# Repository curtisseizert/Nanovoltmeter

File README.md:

# Nanovoltmeter
A low noise nanovoltmeter design files and code

The design includes five boards:
1. The nanovoltmeter main board
2. A SMPS daughter board to downconvert the battery voltage to the various power rails used in the design
3. A battery board with BMS for 4S 21700 cells
4. A rear panel board with battery charger
5. A front panel

This repository will also include the source code for the STM32U575 microcontroller that interfaces with the various peripherals.

Note: The current revision of the board does not work without modifications, but the schematic has been annotated to include these. This project should still be considered in a development state, but the entirety of the design is provided here for anyone seeking to draw upon this work in low-noise, high-resolution voltage sensing projects.

Curent Status
-------------
A revision C to the board is in a stage of occasional development as I finish another project. The new revision will seek to improve the robustness of the design, addressing issues such as the apparent sensitivity to common-mode noise, inadequate power protection leading to cascade failures with certain faults, and minor drift related to battery discharge. I am looking into an improved method of retrieving SPI data from ADC conversions that should allow operation at the maximum sample rate of the AD4030-24 (2 MSPS), to reduce noise and reduce the possibility of aliasing. The revision also includes a minor redesign of the key frontend amplifier to improve gain and stability. The ADR1399 reference option will be removed from this revision.

Version 2.0 of the FW improves handling of results and user inputs, as well as reduces the load on the CPU by making better use of DMA. Unit testing is ongoing and some features are not yet implemented, but they will be coming soon. The command structure uses a SCPI-like syntax but is not fully SCPI-compliant. The improved FW should facilitate more performance testing.

I have built two of these boards, one with an LTC6655 reference, the other with an ADR1399. I have tested the noise and offset performance of the latter both with internal shorts and an external 1 mV reference. Getting both boards to work has required some changes, and I have made the appropriate edits to a revision C schematic though I have not laid this out. The noise and temperature sensitivity of the LTC6655 board is superior for internal shorts. 

Design Background
-----------------

A proof of concept model of the input stage was previously prepared, which showed a flat NSD of approximately 1.2 nV/sqrt(Hz). At 1 sample per second, the peak to peak noise was about 15 nV. The temperature coefficient of the meter was approximately 1 nV/K, but sensitivity to temperature fluctuations was evident and the change in power dissipation as the battery discharged led to a drift of ca. 1 nV/h. This prototype also had a bias current of ~3 nA due to charge injection from the input modulator switch. This revision seeks to change those issues as follows:

1. The main power rails of the board are generated using low noise buck converters (LT8608S) and a Cuk converter on a shielded daughterboard so that the dropout of the on-board LDOs remains consistent through battery discharge
2. Improved layout reduced sensitivity to temperature changes. The input stage is contained in a shielding enclosure and is surrounded by isolation slots. Additionally, the largest power dissipators have been placed outside this shield on opposite sides.
3. The input switching is now handled by a low-capacitance quad MOSFET array (PE4140) using gate drive voltages independently generated with a quad DAC. In a model experiment, it has proven feasible to adjust the DAC switching levels and deadtimes to reduce bias current to <5 pA, though I need to do more work to optimize this aspect.
4. A fast, precision ADC (AD4030-24) now measures the offset error between switching cycles so a 16-bit DAC can control the offset voltage of the input differential amplifier by modulating the channel currents of the input JFETs. In the schematic, the trim range of the DAC is approximately +/-625uV (LSB = 20nV). The low gain of the trimming differential amplifier means the transconductance drops by <1% at the input extremes. This should allow measurement of the trim gain during instrument warmup for single-cycle settling of the control loop.
5. Digital implementation of the control loop also allows one to turn off autozeroing or run the input switching at very low frequencies to minimize charge injection.

Some additional features are:
1. Footprints for two types of voltage references: an ADR1399 for lowest noise/highest stability and an LTC6655 for lower power consumption
2. An optically isolated external trigger input for e.g., synchronizing clocking to powerline cycles.
3. Input protection that engages current limiting to 10 mA (typical, max: 15 mA) at a differential voltage of 2 V for protection against accidentally connecting up to 100V across the terminals. A GDT is included to provide transient protection against higher voltages.
4. Two input ranges: +/-2 mV and +/-20 mV.
5. Reduced power consumption (with LTC6655)

Principle of Operation
----------------------

An input modulator (SW1) switch connects input and feedback signals alternately to the terminals of a high-gain, low-noise discrete JFET differential amplifier. The outputs of the differential amplifier are connected to the terminals of an operational amplifier (U10) via a synchronous demodulator (SW2). The output of the frontend is taken from this op amp. The ADC reads the output voltage from each phase of the modulator. If the difference between the two readings is larger than a deadband value, the controller increments or decrements the Vos DAC (U44) as needed to adjust the channel currents in the input differential amplifier to null the offset of the differential amplifier. The channel currents are controlled by a low-gain transconductance stage formed from U20. To null the offset and 1/f noise of the ADC and associated signal conditioning circuitry, a switch at the inputs to the ADC driver reverses the inputs to this block such that the modulator/demodulator operates at an integer multiple of the input switches for the ADC.

This topology has the effect of modulating the offset voltage (and 1/f noise) of the input stage up to the switching frequency but not modulating the input signal itself. This modulated error signal is minimized by the offset-nulling feedback loop, which dramatically reduces the power at the chopping frequency, and filtered using a cascaded integrator-comb (sinc) filter of user-selectable order (from 1 to 3). Because the input capacitance of the input stage JFETs is fairly large (ca. 75pF), nulling the offset of the differential amplifier also reduces current pulsation at the chopping frequency.

As such, the only theoretical source of offset, drift, or 1/f noise is the op amp connected to the demodulated differential amp outputs, and all these error sources are attentuated by the gain of the differential amplifier, which is about 3500. The input JFETs are paired with PNP BJTs Q16 and Q21 in a Szlikai-like topology to increase the transconductance of the input amplifier to enable it to operate at high gain. The value of drain resistors R91 and R100 is a compromise between noise, gain, and stability; at 133R, each of the eight JFETs operates with a drain current of ca. 1 mA, and the BJTs operate with a collector current of about 1 mA each. Larger resistor values slightly increase moise, increase gain, and decrease phase margin of the overall composite amplifier due to the increase in loop gain.  The op amp used in the design (an ADA4625-1) is a precision, low noise part with low offset and drift, and these error sources are negligible when attenuated by a factor of 3500. With typical spec sheet values, this op amp should contribute about 4 nV offset, 0.06 nV/K temperature coefficient, and give a 1/f noise corner of ca. 0.1 mHz. In practice, the effect of parasitics, especially thermal EMF proves to be a much larger error source, with an uncorrected offset voltage at the front panel of about 250 nV and a 1/f corner of slightly less than 1 mHz (depending on the stability of the ambient temperature). The NSD when measuring the (internally) shorted inputs is <1.2 nV/rt Hz, and with 10s sample periods I have observed p-p noise of just 1.36 nV over 10000 seconds.

Observations
------------

Modulator frequencies in the 600 - 2000 Hz seem to be ideal, and 1800 Hz is set as the default. The inclusion of the deadband in the offset correction loop is necessary to prevent artifacts that appear in the spectrum of the analog output. The key issue seems to be sensitivity to some noise source at low frequency (probably the SMPS, perhaps also 60 Hz pickup). Modulator frequencies up to 14.4 kHz are possible, but these lead to increases in noise as the settling time of the frontend and ADC signal conditioning circuits takes up an increasing percentage of the potential conversion time.

NSD without deadband, showing aliasing of V_os correction loop

The biggest limitation in the utility of the instrument is the considerable increase in noise and change in offset that occurs when something is connected to the front panel. This effect occurs regardless of whether the input relay is measuring an internal short. It seems most likely that the case, which is tied to protective earth via the USB cable shield is shifting in potential relative to circuit ground, and this is capacitively coupling to something sensitive. However, connecting the USB cable through an isolator, which disconnects the shield from PE, actually makes the noise situation worse rather than better. 

Implementation of a Sinc2 filter improved some apparent aliasing artifacts that were present in the spectrum at very low (<10 mHz) frequencies. Use of a Sinc3 filter did not lead to any noticeable improvents. The flatness of the noise spectrum (with an internal short) to below 1 mHz was very repeatable provided that environmental conditions were suitably stable.

While the nanovoltmenter has an offset temperature coefficient of <1 nV/K, it does show some sensitivity to changes in the rate of temperature change (i.e., the offset voltage correlates to the second derivative of temperature with respect to time). This makes sense because those changes lead to changes in temperature gradients across the board, which influences parasitic thermocouple behavior at the input. The power supply is also somewhat more efficient at lower input voltages, which leads to reduced heat dissipation as the batteries discharge, influencing the offset. In very long captures, such as the LTC6655 reference example shown below, this leads to a drift of <0.1 nV/h. It is notable that the overall drift in this 100h capture was only about 8 nV despite about 2.5 K fluctuation in input temperature over that time.

The linearity of the amplifier is expected to be quite good as the offset correction loop keeps the input terminals of the frontend amplifier at the same voltage regardless of input. The main source of nonlinearity should be the gain setting resistors, as temperature changes due to increased power dissipation may lead to changes the resistor ratio and the gain of the frontend. To test the linearity of the amplifier, I used a highly accurate source based on an LTZ1000A and DAC11001B with a tested linearity error of <2 ppm and a 200K/20R divider to reduce the output voltage range to 0 to 1 mV. I averaged several 11 point sweeps over this range to obtain a maximum linearity error of 1.5 ppm. The averaging was necessary due the increased noise seen with something plugged in to the front panel. The increased sensitivity of the lower gain +/-20 mV range to external noise sources (probably due to reduced stability of the amplifier at lower gain) meant that determining linearity error for this range was not practical. In all measurements of external sources, I found it was optimal to wrap the test lead around a nanocrystalline toroid, which did reduce noise considerably.

Performance Reductions with External Measurements
-------------------------------------------------

Taken together, my observations about the difficulty of performing measurements with external sources are difficult to untangle and may point to multiple simultaneous issues. I have collected them here to try to provide some insight into this behavior and possible solutions:
1. The 40 dB gain range is more sensitive than the 60 dB gain range. The lower gain range has lower phase margin and still takes 60 dB gain at higher frequencies, as this was necessary to ensure stability of the amplifier at lower gain. This points to stability related problems, such as degradation of phase margin (leading to ringing, etc. after switching events) when the amplifier sees an inductive source impedance. Inductive sources present a considerable challenge with such amplifiers because of the large gate-source capacitance of the paralleled JFETs. This can give resonant gain with inductive inputs.
2. The improvement in performance when using a common mode choke on the input suggests an effect from frequencies well above the amplifier's passband. The inductance of the common mode choke was likely aorund 800 uH, which would present negligible impedance at 60 Hz.
3. I recorded spectra from the analog outputs with the instrument powered by a bench power supply to remove SMPS signals. With 60 dB gain on the frontend and the 10 nF input capacitor switched off, the peaks at harmonics of the chopping frequency were about 20 dB higher with an external short than with an internal short. This is presumably an effect of inductance at the input as there are ferrite beads in the input protection circuitry between the internal and external shorts. Some of these artifacts may lead to aliasing.
Internal Short Analog Output, Gain = 1000

External Short Analog Output, Gain = 1000
4. Plugging a source into the input leads to a shift in offset with an internal short (ca. 200 nV). The source of this effect is not clear. The source mentioned in the linearity test section actually has an internal 100:1 attenuator for low voltages, but directly plugging the source into the NVM gave such large increases in noise that it would not be practical to measure ppm level offsets. The input connector is a LEMO-0S-304 type with the shell of the connector electically connected to the instrument chassis, which is itself connected to protective earth via the USB cable. In general, cables with the shield connected at both ends gave significantly poorer performance than those with the shield left unconnected at one end, suggesting that connection of the two chassis grounds was problematic despite their isolation from circuit ground. The use of nylon screws to connect the USB connector to the rear panel of the source (and hence remove the connection to protective earth) was necessary for reliable results in that case. Most of the sensitive circuitry of the input is very well shielded against electrostatic pickup by the use of board-level RF shields, but the input protection circuitry and switching relays, as well as the chopper demodulator and op amp, are outside of these shields. A ground loop is not necesasary to cause this effect, as it is observed even when an unconnected cable is plugged into the front panel. Some additional tests are necessary to determine the minimum configuration needed to cause this shift (e.g., does the behavior occur with just connection of the shell, or do the actual input leads (which provide a connection to the board) need to be connected as well? If it seems that additional shielding is needed to reduce this effect, it may be difficult to maintain the same form factor.

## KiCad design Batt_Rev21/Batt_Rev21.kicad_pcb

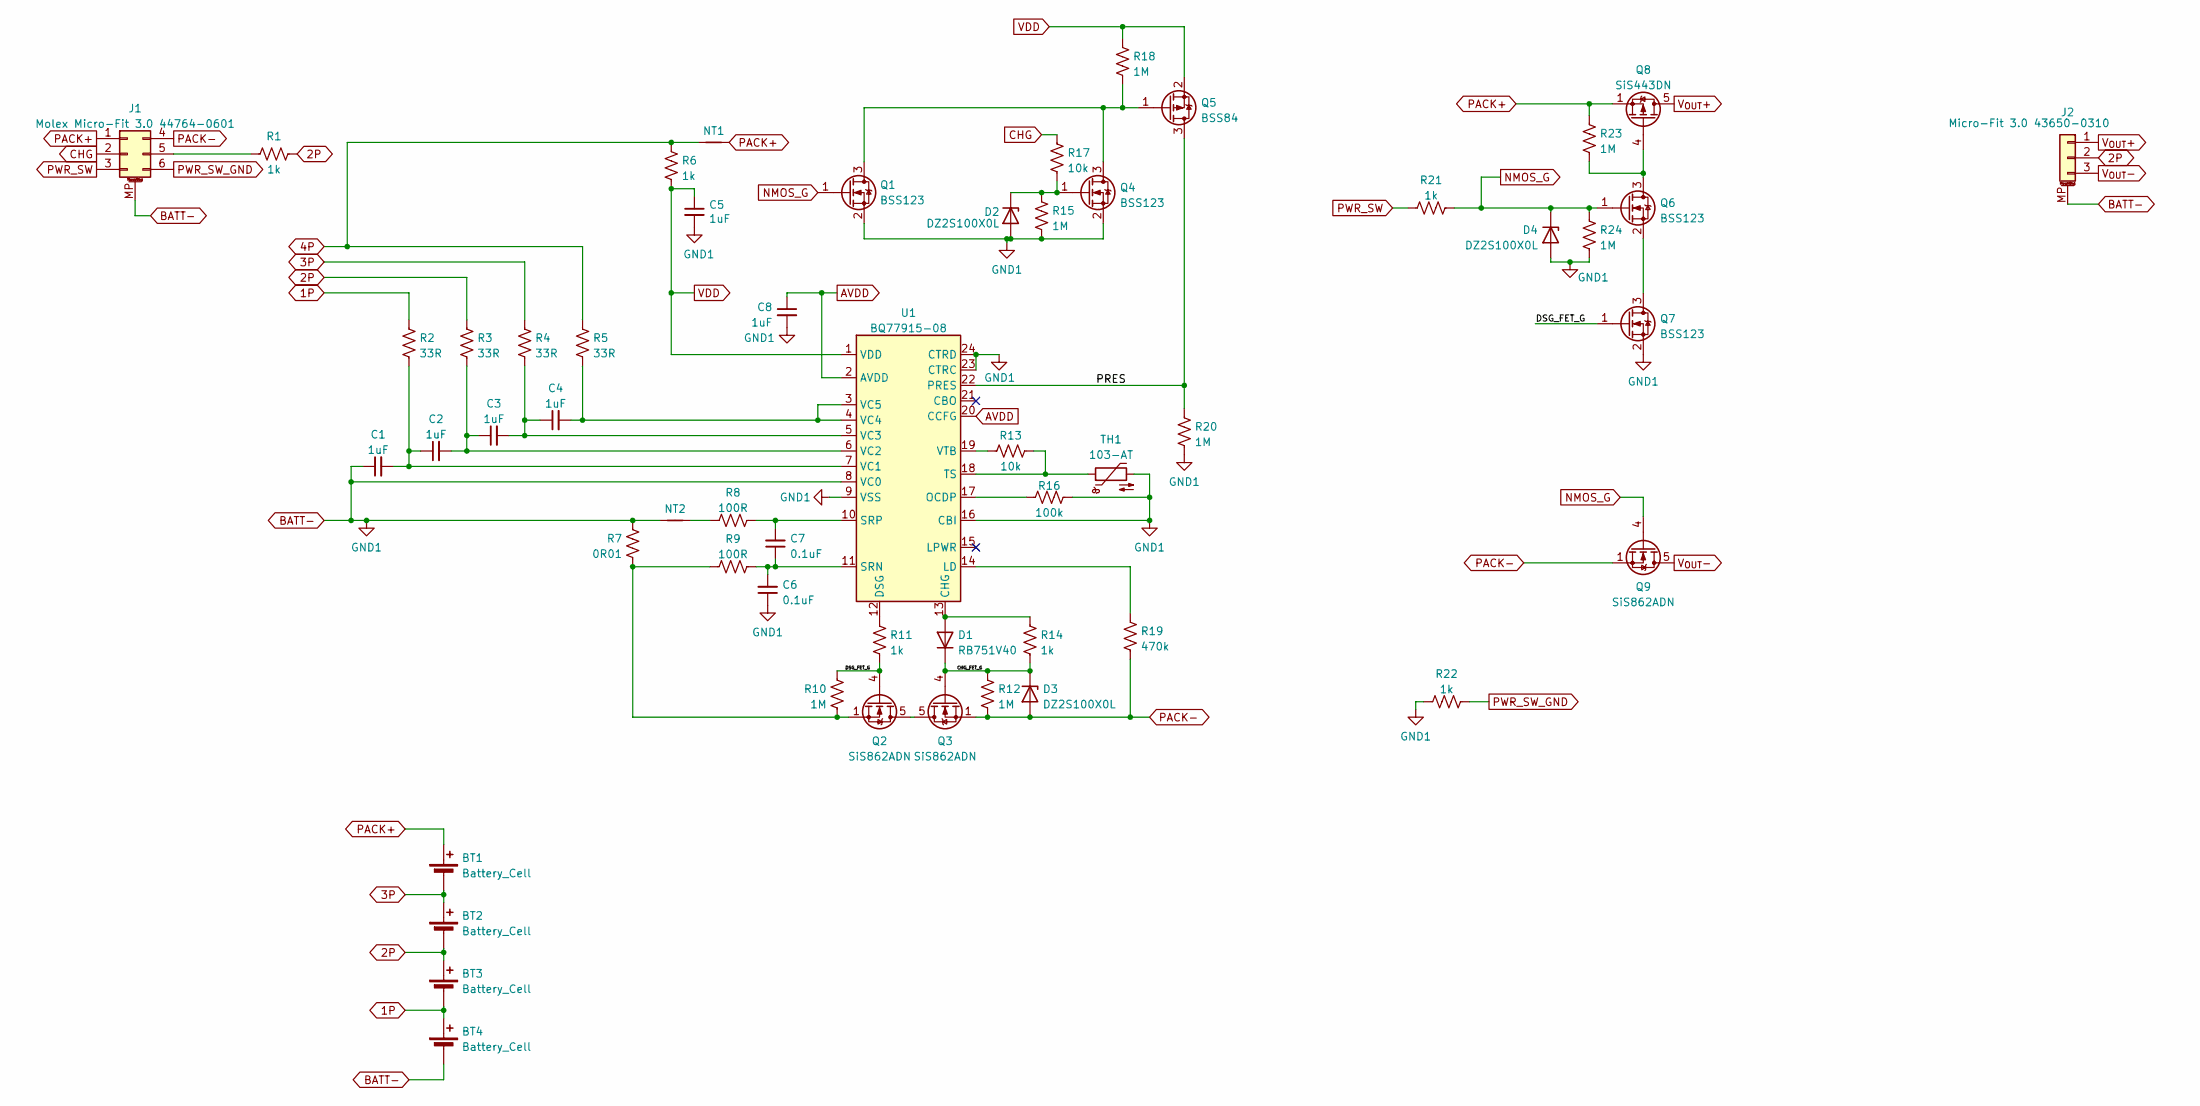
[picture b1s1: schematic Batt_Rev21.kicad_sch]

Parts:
BT1, BT2, BT3, BT4: Battery_Cell; BatteryHolder_Keystone246_21700
C1, C2, C3, C4, C5, C8: 1uF; C_0603_1608Metric
C6, C7: 0.1uF; C_0603_1608Metric
D1: RB751V40; D_SOD-323
D2, D3, D4: DZ2S100X0L; D_SOD-523
J1: Molex Micro-Fit 3.0 44764-0601; Molex_Micro-Fit_3.0_44764-0601-0600_2x03_P3.00mm_Horizontal
J2: Micro-Fit 3.0 43650-0310; Molex_Micro-Fit_3.0_43650-0310_1x03-1MP_P3.00mm_Horizontal
NT1, NT2: Net-Tie_2; NetTie-2_SMD_Pad0.2mm
Q1, Q4, Q6, Q7: BSS123; SOT-23
Q2, Q3, Q9: SiS862ADN; Vishay_PowerPAK_1212-8_Single
Q5: BSS84; SOT-23
Q8: SiS443DN; Vishay_PowerPAK_1212-8_Single
R1, R6, R11, R14, R21, R22: 1k; R_0603_1608Metric_Outline
R2, R3, R4, R5: 33R; R_0603_1608Metric_Outline
R7: 0R01; R_1206_3216Metric
R8, R9: 100R; R_0603_1608Metric_Outline
R10, R12, R15, R18, R20, R23, R24: 1M; R_0603_1608Metric_Outline
R13, R17: 10k; R_0603_1608Metric_Outline
R16: 100k; R_0603_1608Metric_Outline
R19: 470k; R_0603_1608Metric_Outline
TH1: 103-AT; R_0603_1608Metric_Outline
U1: BQ77915-08; TSSOP-24_4.4x7.8mm_P0.65mm

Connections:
1P: BT3.1 (-), BT4.2 (+), R2.1
2P: BT2.1 (-), BT3.2 (+), J2.2, R1.1, R3.1
3P: BT1.1 (-), BT2.2 (+), R4.1
4P: NT1.2, R5.1, R6.1
/CHG_FET_G: D1.1 (K), D3.1 (K), Q3.4 (G), R12.1, R14.2
/DSG_FET_G: Q2.4 (G), Q7.1 (G), R10.1, R11.2
/PRES: Q5.3 (D), R20.1, U1.22 (PRES)
AVDD: C8.1, U1.2 (AVDD), U1.20 (CCFG)
BATT-: BT4.1 (-), C1.1, C5.2, C6.1, C8.2, D2.2 (A), D4.2 (A), J1.MP (MountPin), J2.MP (MountPin), NT2.2, Q1.2 (S), Q4.2 (S), Q7.2 (S), R7.1, R15.2, R16.1, R20.2, R22.1, R24.2, TH1.2, U1.8 (VC0), U1.9 (VSS), U1.16 (CBI), U1.23 (CTRC), U1.24 (CTRD)
CHG: J1.2, R17.1
NMOS_G: D4.1 (K), Q1.1 (G), Q6.1 (G), Q9.4 (G), R21.2, R24.1
unnamed: D1.2 (A), R14.1, U1.13 (CHG)
unnamed: D2.1 (K), Q4.1 (G), R15.1, R17.2
unnamed: J1.5, R1.2
unnamed: NT2.1, R8.1
unnamed: Q1.3 (D), Q4.3 (D), Q5.1 (G), R18.2
unnamed: Q2.5 (D), Q3.5 (D)
unnamed: Q2.1 (S), Q2.2 (S), Q2.3 (S), R7.2, R9.2, R10.2
unnamed: Q6.3 (D), Q8.4 (G), R23.2
unnamed: Q6.2 (S), Q7.3 (D)
unnamed: R11.1, U1.12 (DSG)
unnamed: R19.1, U1.14 (LD)
unnamed: R16.2, U1.17 (OCDP)
unnamed: C6.2, C7.1, R9.1, U1.11 (SRN)
unnamed: C7.2, R8.2, U1.10 (SRP)
unnamed: R13.1, TH1.1, U1.18 (TS)
unnamed: C1.2, C2.1, R2.2, U1.7 (VC1)
unnamed: C2.2, C3.1, R3.2, U1.6 (VC2)
unnamed: C3.2, C4.1, R4.2, U1.5 (VC3)
unnamed: C4.2, R5.2, U1.3 (VC5), U1.4 (VC4)
unnamed: R13.2, U1.19 (VTB)
PACK+: BT1.2 (+), J1.1, NT1.1, Q8.1 (S), Q8.2 (S), Q8.3 (S), R23.1
PACK-: D3.2 (A), J1.4, Q3.1 (S), Q3.2 (S), Q3.3 (S), Q9.1 (S), Q9.2 (S), Q9.3 (S), R12.2, R19.2
PWR_SW: J1.3, R21.1
PWR_SW_GND: J1.6, R22.2
VDD: C5.1, Q5.2 (S), R6.2, R18.1, U1.1 (VDD)
V_{OUT}+: J2.1, Q8.5 (D)
V_{OUT}-: J2.3, Q9.5 (D)

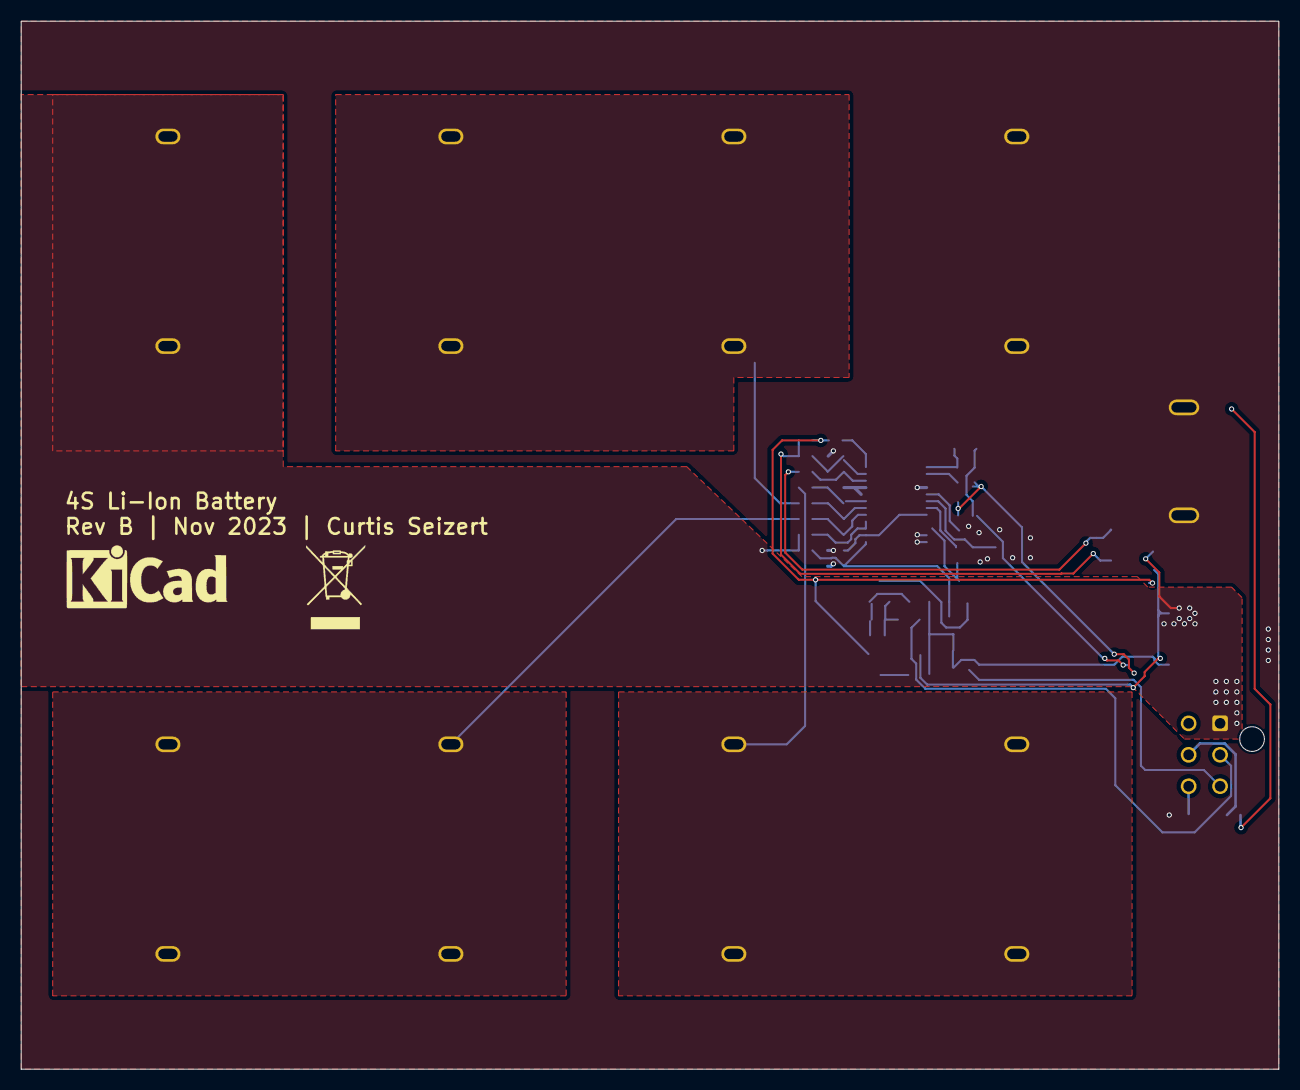
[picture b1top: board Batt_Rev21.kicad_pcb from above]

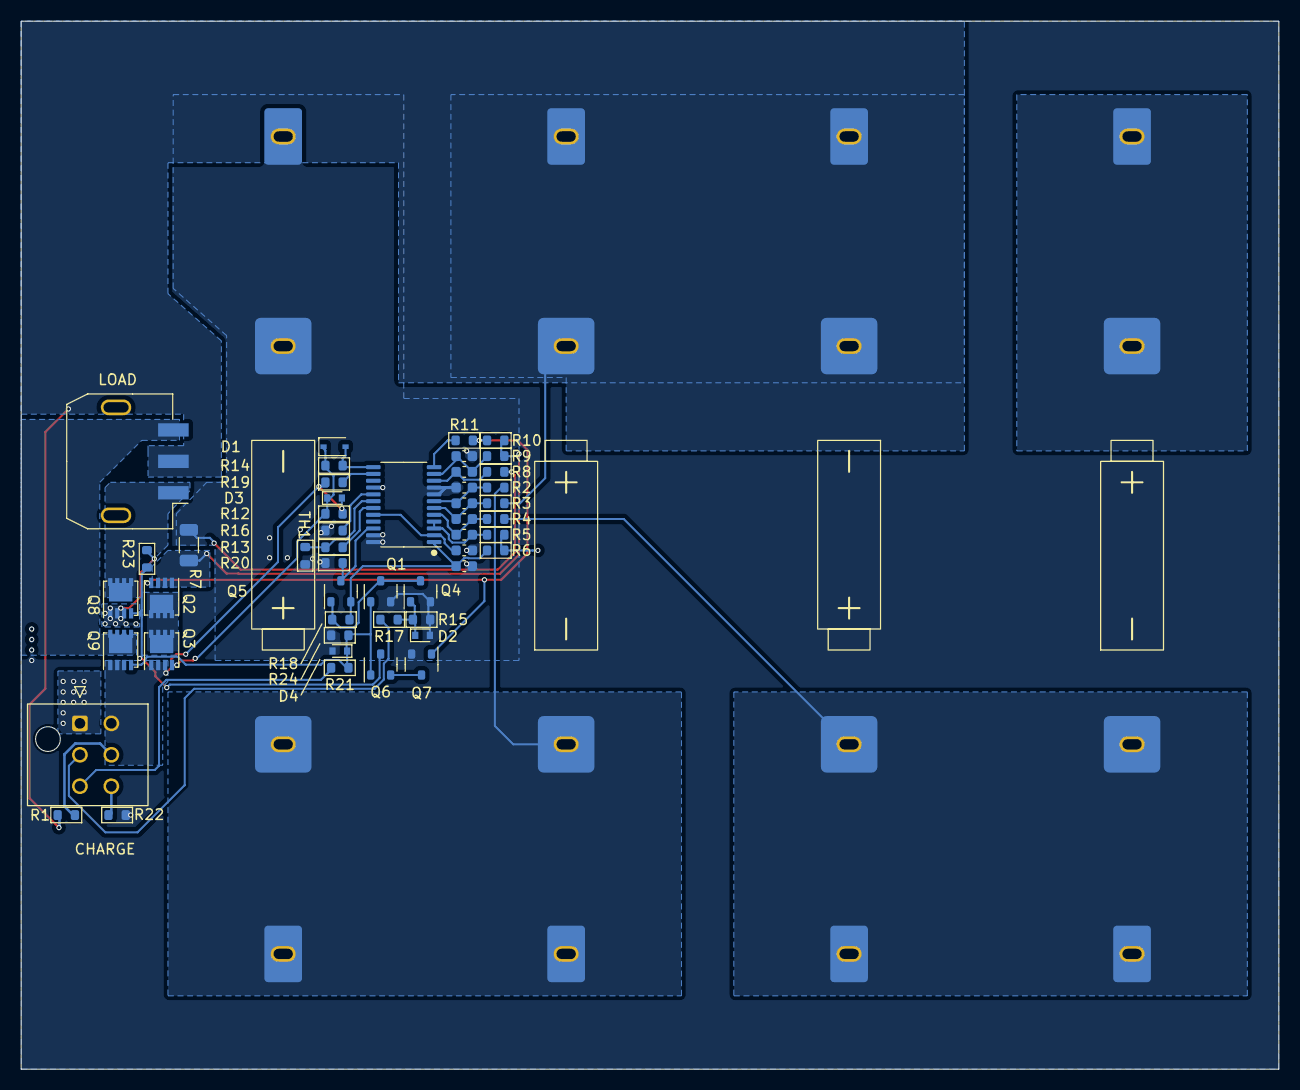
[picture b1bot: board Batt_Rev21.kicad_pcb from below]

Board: 2 copper layers, 120.0 x 100.0 mm, 55 parts (55 on the bottom side), 38 nets.

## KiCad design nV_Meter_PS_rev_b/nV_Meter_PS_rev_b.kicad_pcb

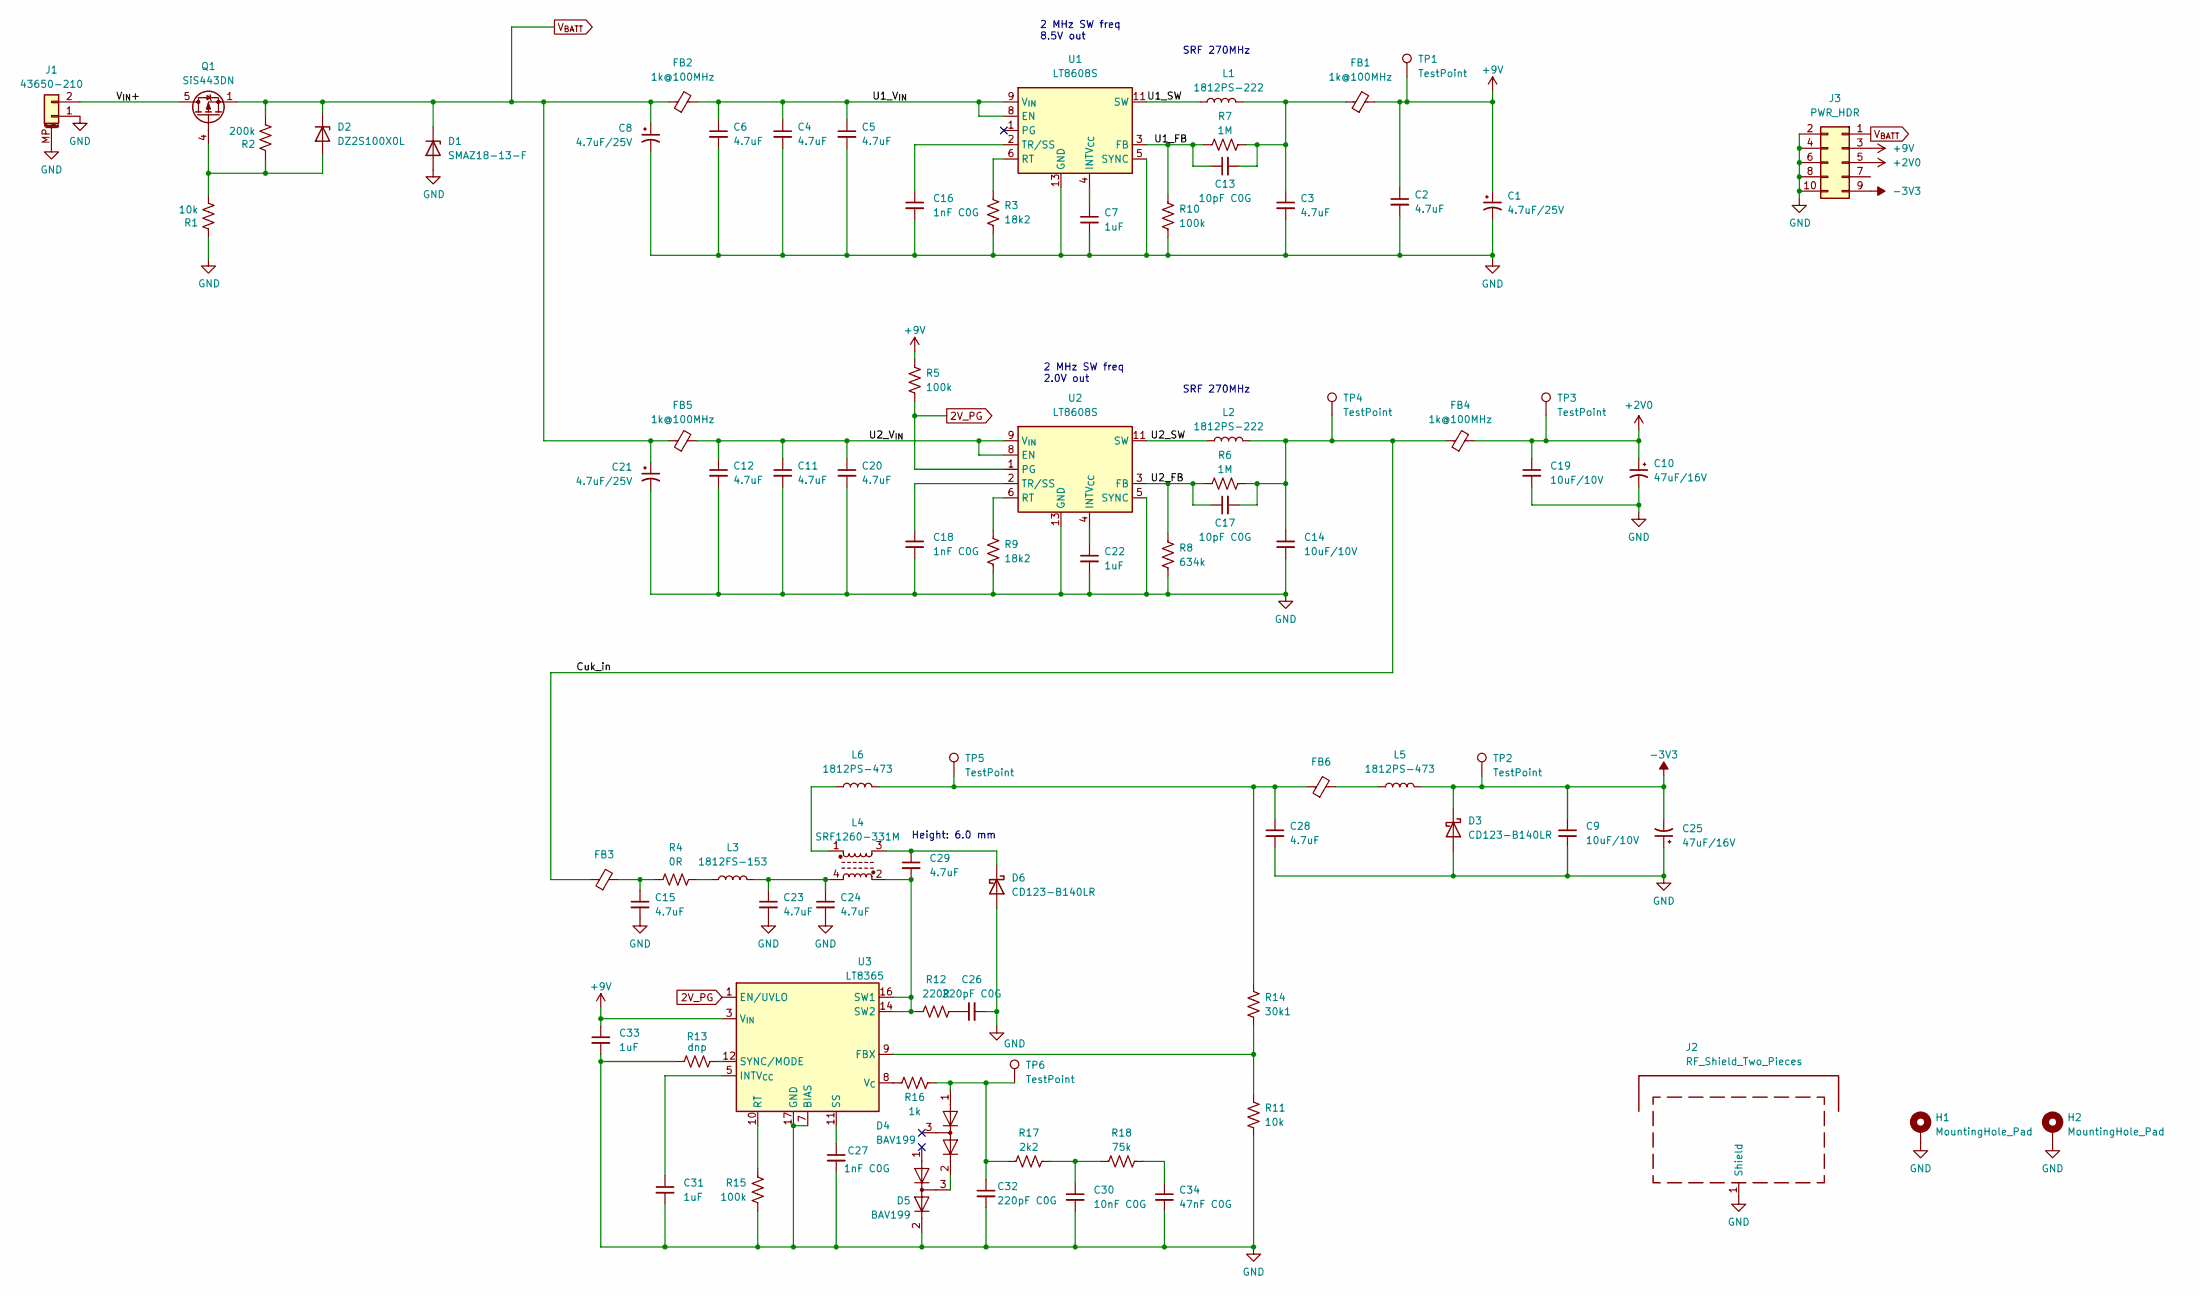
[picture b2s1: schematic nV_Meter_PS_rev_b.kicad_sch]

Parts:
C1, C8, C21: 4.7uF/25V; CP_EIA-3528-12_Kemet-T; Part Number x
C2, C3, C4, C5, C6, C11, C12, C15, C20, C23, C24, C28, C29: 4.7uF; C_0805_2012Metric; Part Number GRM21BZ7YA475KE15K
C7, C22, C31, C33: 1uF; C_0402_1005Metric; Part Number GRM155R61H105KE05D
C9, C14, C19: 10uF/10V; C_0805_2012Metric; Part Number x
C10, C25: 47uF/16V; CP_EIA-3528-12_AVX_B_Conformal; Part Number F951C476MBAAQ2
C13, C17: 10pF C0G; C_0402_1005Metric; Part Number GRM1555C1H100JA01D
C16, C18, C27: 1nF C0G; C_0402_1005Metric; Part Number GRM1555C1H102JA01J
C26, C32: 220pF C0G; C_0402_1005Metric; Part Number GRM1555C1H221JA01J
C30: 10nF C0G; C_0402_1005Metric; Part Number x
C34: 47nF C0G; C_0805_2012Metric; Part Number x
D1: SMAZ18-13-F; D_SOD-123F; Part Number HPZR-C18-QX
D2: DZ2S100X0L; D_SOD-523; Part Number x
D3, D6: CD123-B140LR; D_PowerDI-123; Part Number CD123-B140LR
D4, D5: BAV199; SOT-23; Part Number x
FB1, FB2, FB3, FB4, FB5, FB6: 1k@100MHz; L_1206_3216Metric; Part Number HZ1206D102R-10
H1, H2: MountingHole_Pad; MountingHole_2.2mm_M2_Pad_Via
J1: 43650-210; Molex_Micro-Fit_3.0_43650-0210_1x02-1MP_P3.00mm_Horizontal
J2: RF_Shield_Two_Pieces; Orbel_L-1750TB2250
J3: PWR_HDR; PinHeader_2x05_P2.54mm_Vertical
L1, L2: 1812PS-222; L_1812_4532Metric
L3: 1812FS-153; L_1812_4532Metric
L4: SRF1260-331M; L_Bourns_SRF1260
L5, L6: 1812PS-473; L_1812_4532Metric
Q1: SiS443DN; Vishay_PowerPAK_1212-8_Single
R1, R11: 10k; R_0402_1005Metric; Part Number RT0402FRE0710KL
R2: 200k; R_0402_1005Metric; Part Number MCS04020C2003FE000
R3, R9: 18k2; R_0402_1005Metric; Part Number RC0402FR-1318K2L
R4: 0R; R_1206_3216Metric_red; Part Number x
R5, R10, R15: 100k; R_0402_1005Metric; Part Number RT0402FRE07100KL
R6, R7: 1M; R_0402_1005Metric; Part Number RC0402FR-7W1ML
R8: 634k; R_0402_1005Metric; Part Number RC0402FR-07634KL
R12: 220R; R_0402_1005Metric; Part Number RC0402JR-7D220RL
R13: dnp; R_0402_1005Metric; Part Number x
R14: 30k1; R_0402_1005Metric; Part Number RR0510P-3012-D
R16: 1k; R_0402_1005Metric; Part Number RR0510P-102-D
R17: 2k2; R_0402_1005Metric; Part Number RC0402JR-072K2L
R18: 75k; R_0402_1005Metric; Part Number RC0402JR-0775KL
TP1, TP2, TP3, TP4, TP5, TP6: TestPoint; TestPoint_Pad_D1.0mm
U1, U2: LT8608S; Linear_LQFN12_2x3mm_0.5x1.45mmEP
U3: LT8365; MSOP-12-16-1EP_3x4mm_P0.5mm_EP1.65x2.85mm

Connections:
2V_PG: R5.1, U2.1 (PG), U3.1 (EN/UVLO)
+2V0: C10.1, C19.1, FB4.2, J3.5, TP3.1
+9V: C1.1, C2.1, C33.1, FB1.2, J3.3, R5.2, TP1.1, U3.3 (V_{IN})
-3V3: C9.1, C25.2, D3.1 (K), J3.9, L5.2, TP2.1
/Cuk_in: C14.1, C17.2, FB3.1, FB4.1, L2.2, R6.2, TP4.1
/U1_FB: C13.1, R7.1, R10.2, U1.3 (FB)
/U1_SW: L1.1, U1.11 (SW), U1.12 (SW)
/U1_V_{IN}: C4.1, C5.1, C6.1, FB2.2, U1.8 (EN), U1.9 (V_{IN}), U1.10 (V_{IN})
/U2_FB: C17.1, R6.1, R8.2, U2.3 (FB)
/U2_SW: L2.1, U2.11 (SW), U2.12 (SW)
/U2_V_{IN}: C11.1, C12.1, C20.1, FB5.2, U2.8 (EN), U2.9 (V_{IN}), U2.10 (V_{IN})
/V_{IN}+: J1.2, Q1.5 (D)
GND: C1.2, C2.2, C3.2, C4.2, C5.2, C6.2, C7.2, C8.2, C9.2, C10.2, C11.2, C12.2, C14.2, C15.2, C16.2, C18.2, C19.2, C20.2, C21.2, C22.2, C23.2, C24.2, C25.1, C26.2, C27.2, C28.2, C30.2, C31.2, C32.2, C33.2, C34.2, D1.2 (A), D3.2 (A), D5.2 (A), D6.2 (A), H1.1, H2.1, J1.1, J1.MP (MountPin), J2.1 (Shield), J3.2, J3.4, J3.6, J3.8, J3.10, R1.1, R3.1, R8.1, R9.1, R10.1, R11.1, R13.2, R15.1, U1.5 (SYNC), U1.7 (GND), U1.13 (GND), U2.5 (SYNC), U2.7 (GND), U2.13 (GND), U3.7 (BIAS), U3.17 (GND)
unnamed: C3.1, C13.2, FB1.1, L1.2, R7.2
unnamed: C15.1, FB3.2, R4.2
unnamed: C23.1, C24.1, L3.2, L4.4
unnamed: C26.1, R12.1
unnamed: C28.1, FB6.1, L6.2, R14.2, TP5.1
unnamed: C30.1, R17.1, R18.2
unnamed: C32.1, D4.1 (K), R16.2, R17.2, TP6.1
unnamed: C34.1, R18.1
unnamed: D2.2 (A), Q1.4 (G), R1.2, R2.1
unnamed: D4.2 (A), D5.3 (K)
unnamed: C29.1, D6.1 (K), L4.3
unnamed: FB6.2, L5.1
unnamed: L3.1, R4.1
unnamed: L4.1, L6.1
unnamed: C7.1, U1.4 (INTV_{CC})
unnamed: R3.2, U1.6 (RT)
unnamed: C16.1, U1.2 (TR/SS)
unnamed: C22.1, U2.4 (INTV_{CC})
unnamed: R9.2, U2.6 (RT)
unnamed: C18.1, U2.2 (TR/SS)
unnamed: R11.2, R14.1, U3.9 (FBX)
unnamed: C31.1, U3.5 (INTV_{CC})
unnamed: R15.2, U3.10 (RT)
unnamed: C27.1, U3.11 (SS)
unnamed: C29.2, L4.2, R12.2, U3.14 (SW2), U3.16 (SW1)
unnamed: R13.1, U3.12 (SYNC/MODE)
unnamed: R16.1, U3.8 (V_{C})
V_{BATT}: C8.1, C21.1, D1.1 (K), D2.1 (K), FB2.1, FB5.1, J3.1, Q1.1 (S), Q1.2 (S), Q1.3 (S), R2.2

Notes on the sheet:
Height: 6.0 mm
SRF 270MHz
2 MHz SW freq 8.5V out
2 MHz SW freq 2.0V out

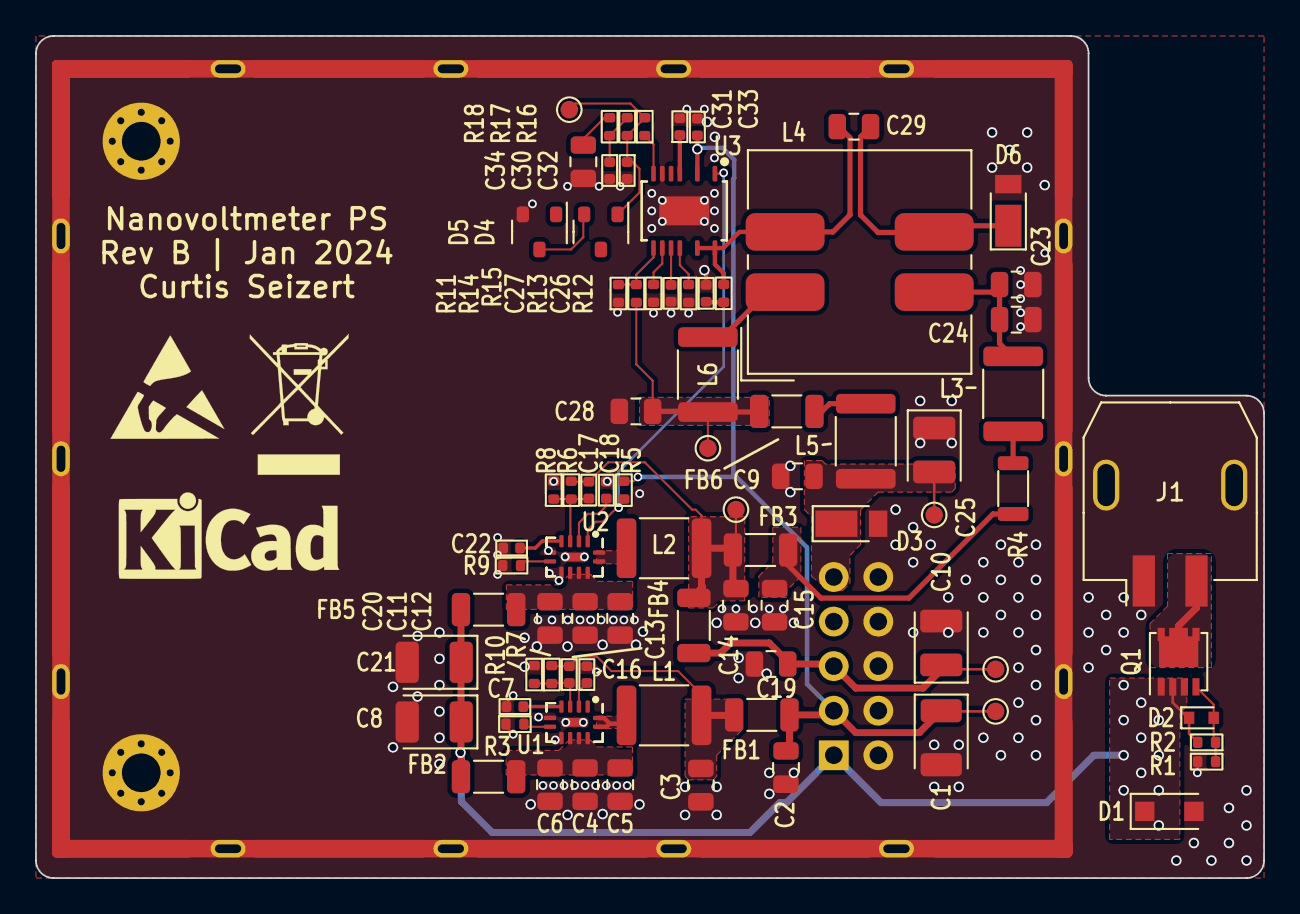
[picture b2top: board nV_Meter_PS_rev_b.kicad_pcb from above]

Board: 4 copper layers, 70.0 x 48.0 mm, 85 parts (1 on the bottom side), 41 nets.
